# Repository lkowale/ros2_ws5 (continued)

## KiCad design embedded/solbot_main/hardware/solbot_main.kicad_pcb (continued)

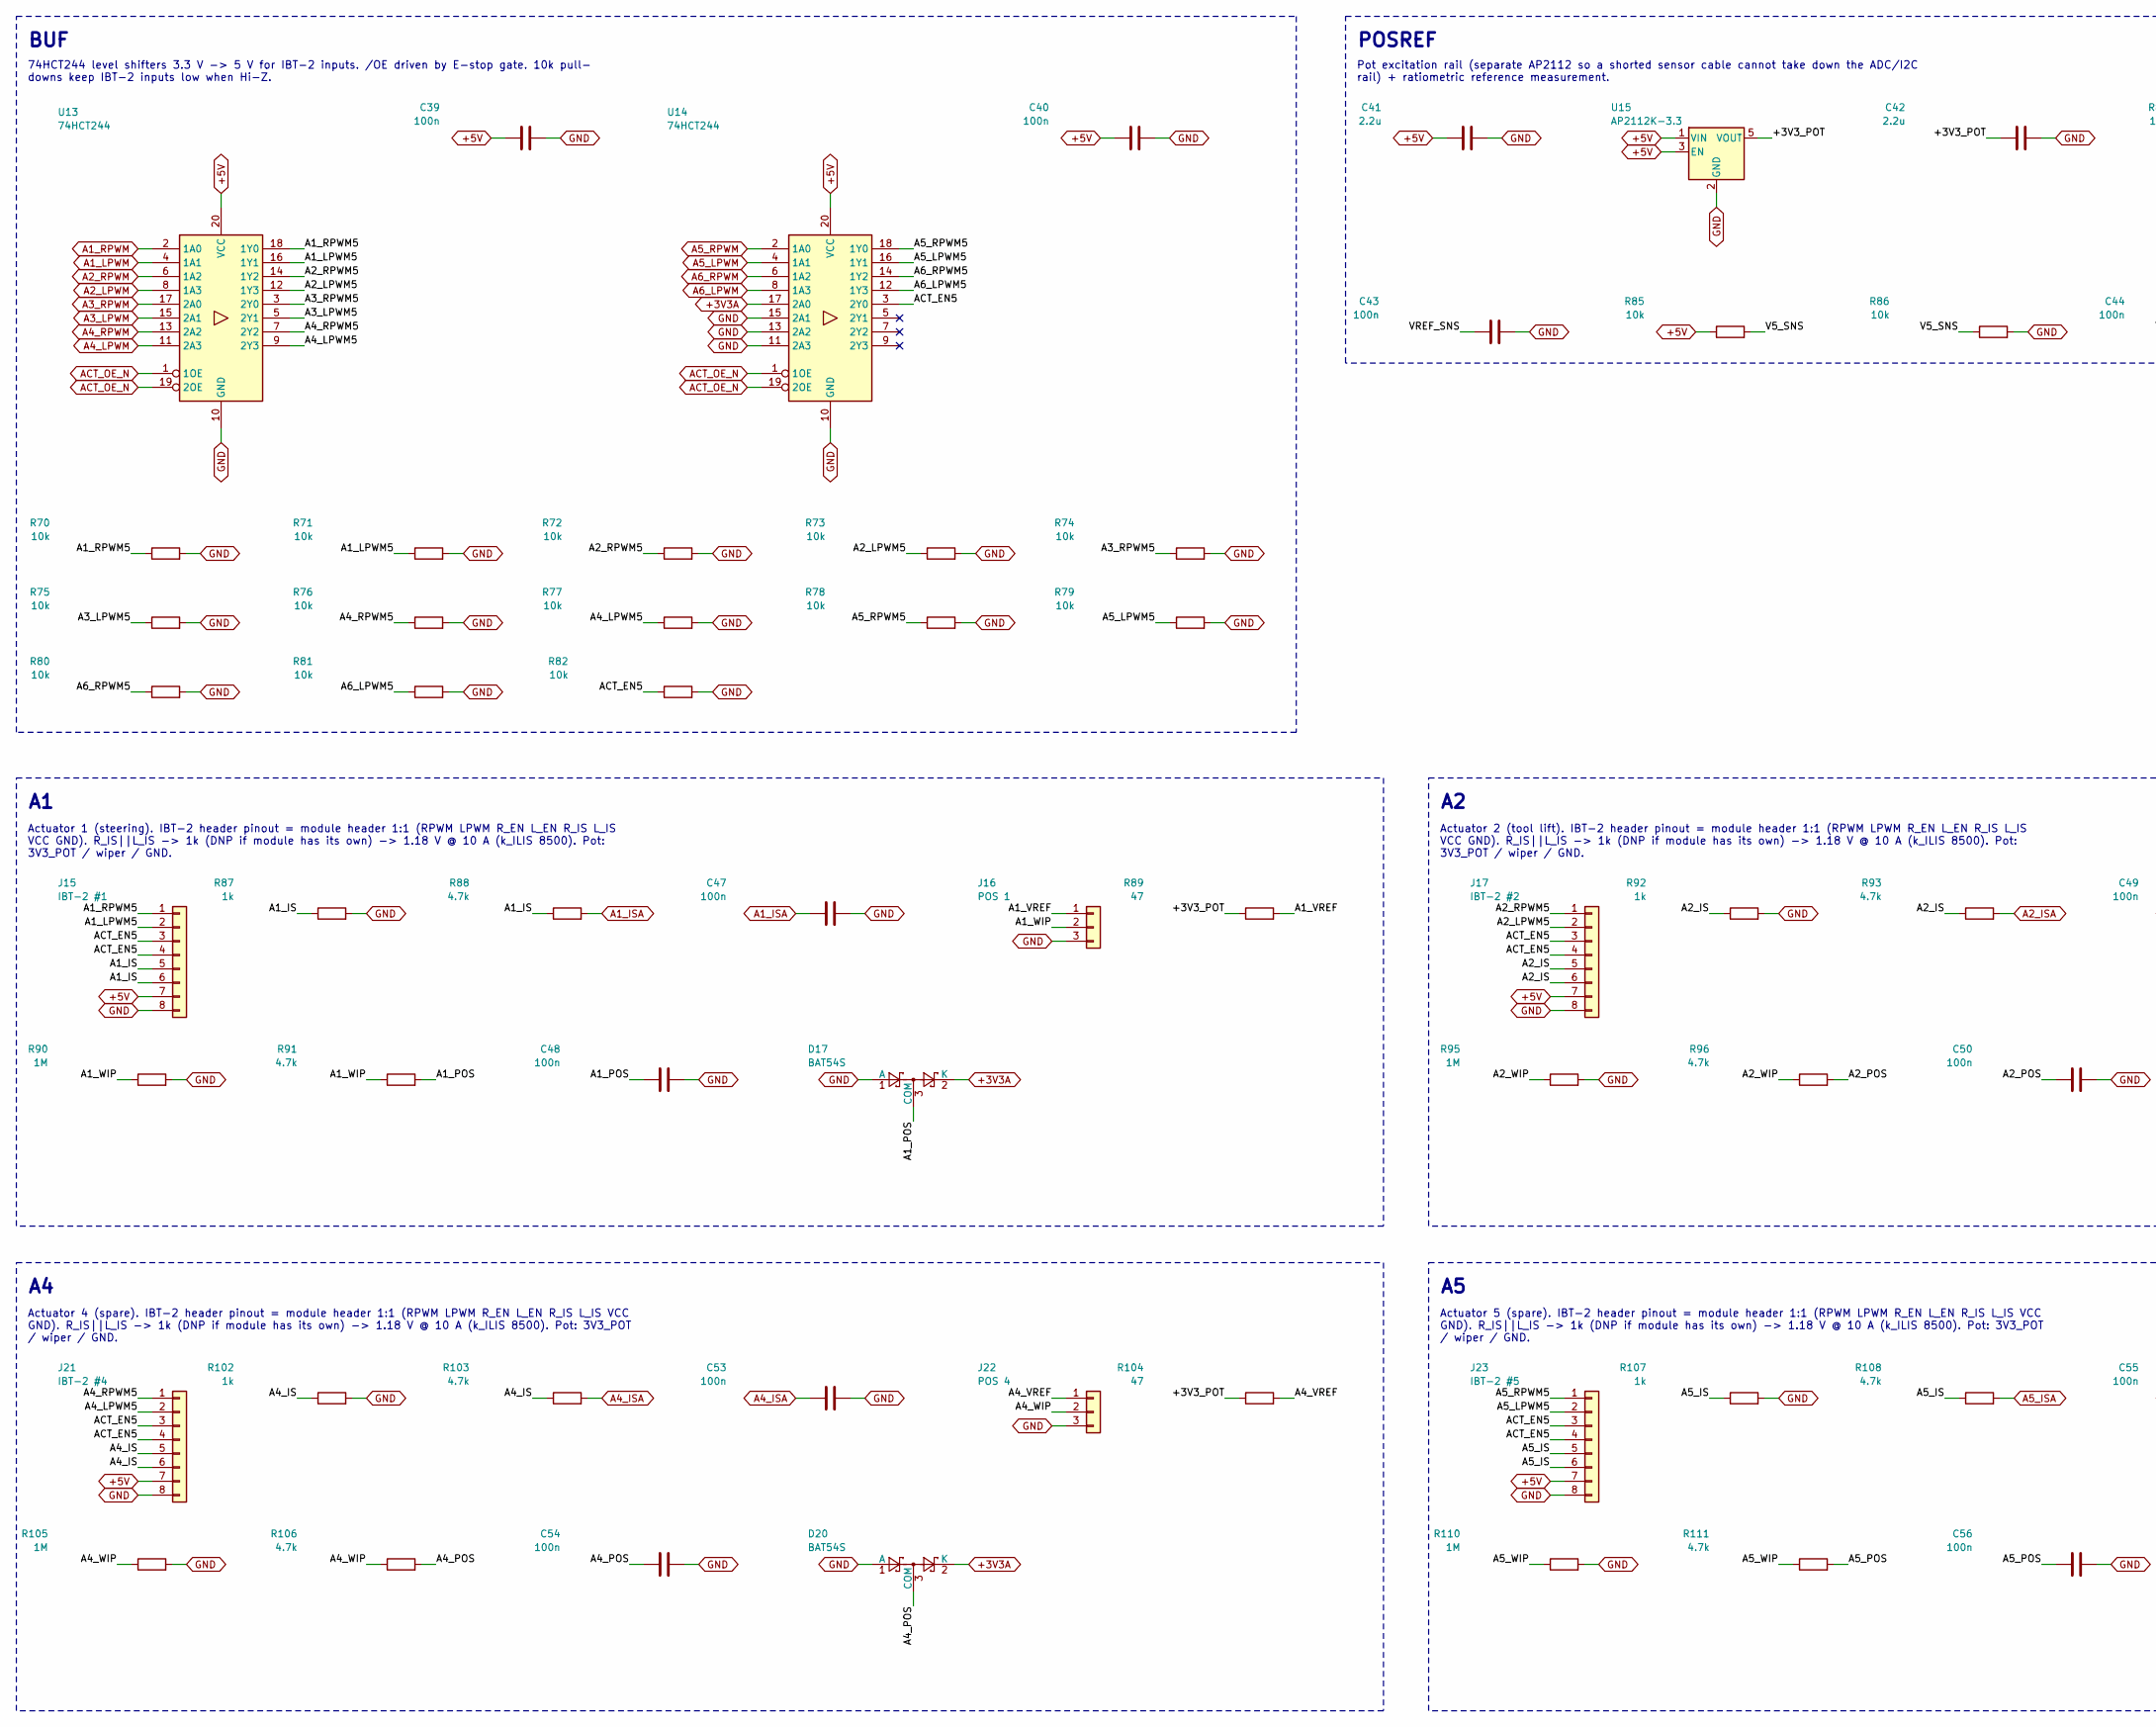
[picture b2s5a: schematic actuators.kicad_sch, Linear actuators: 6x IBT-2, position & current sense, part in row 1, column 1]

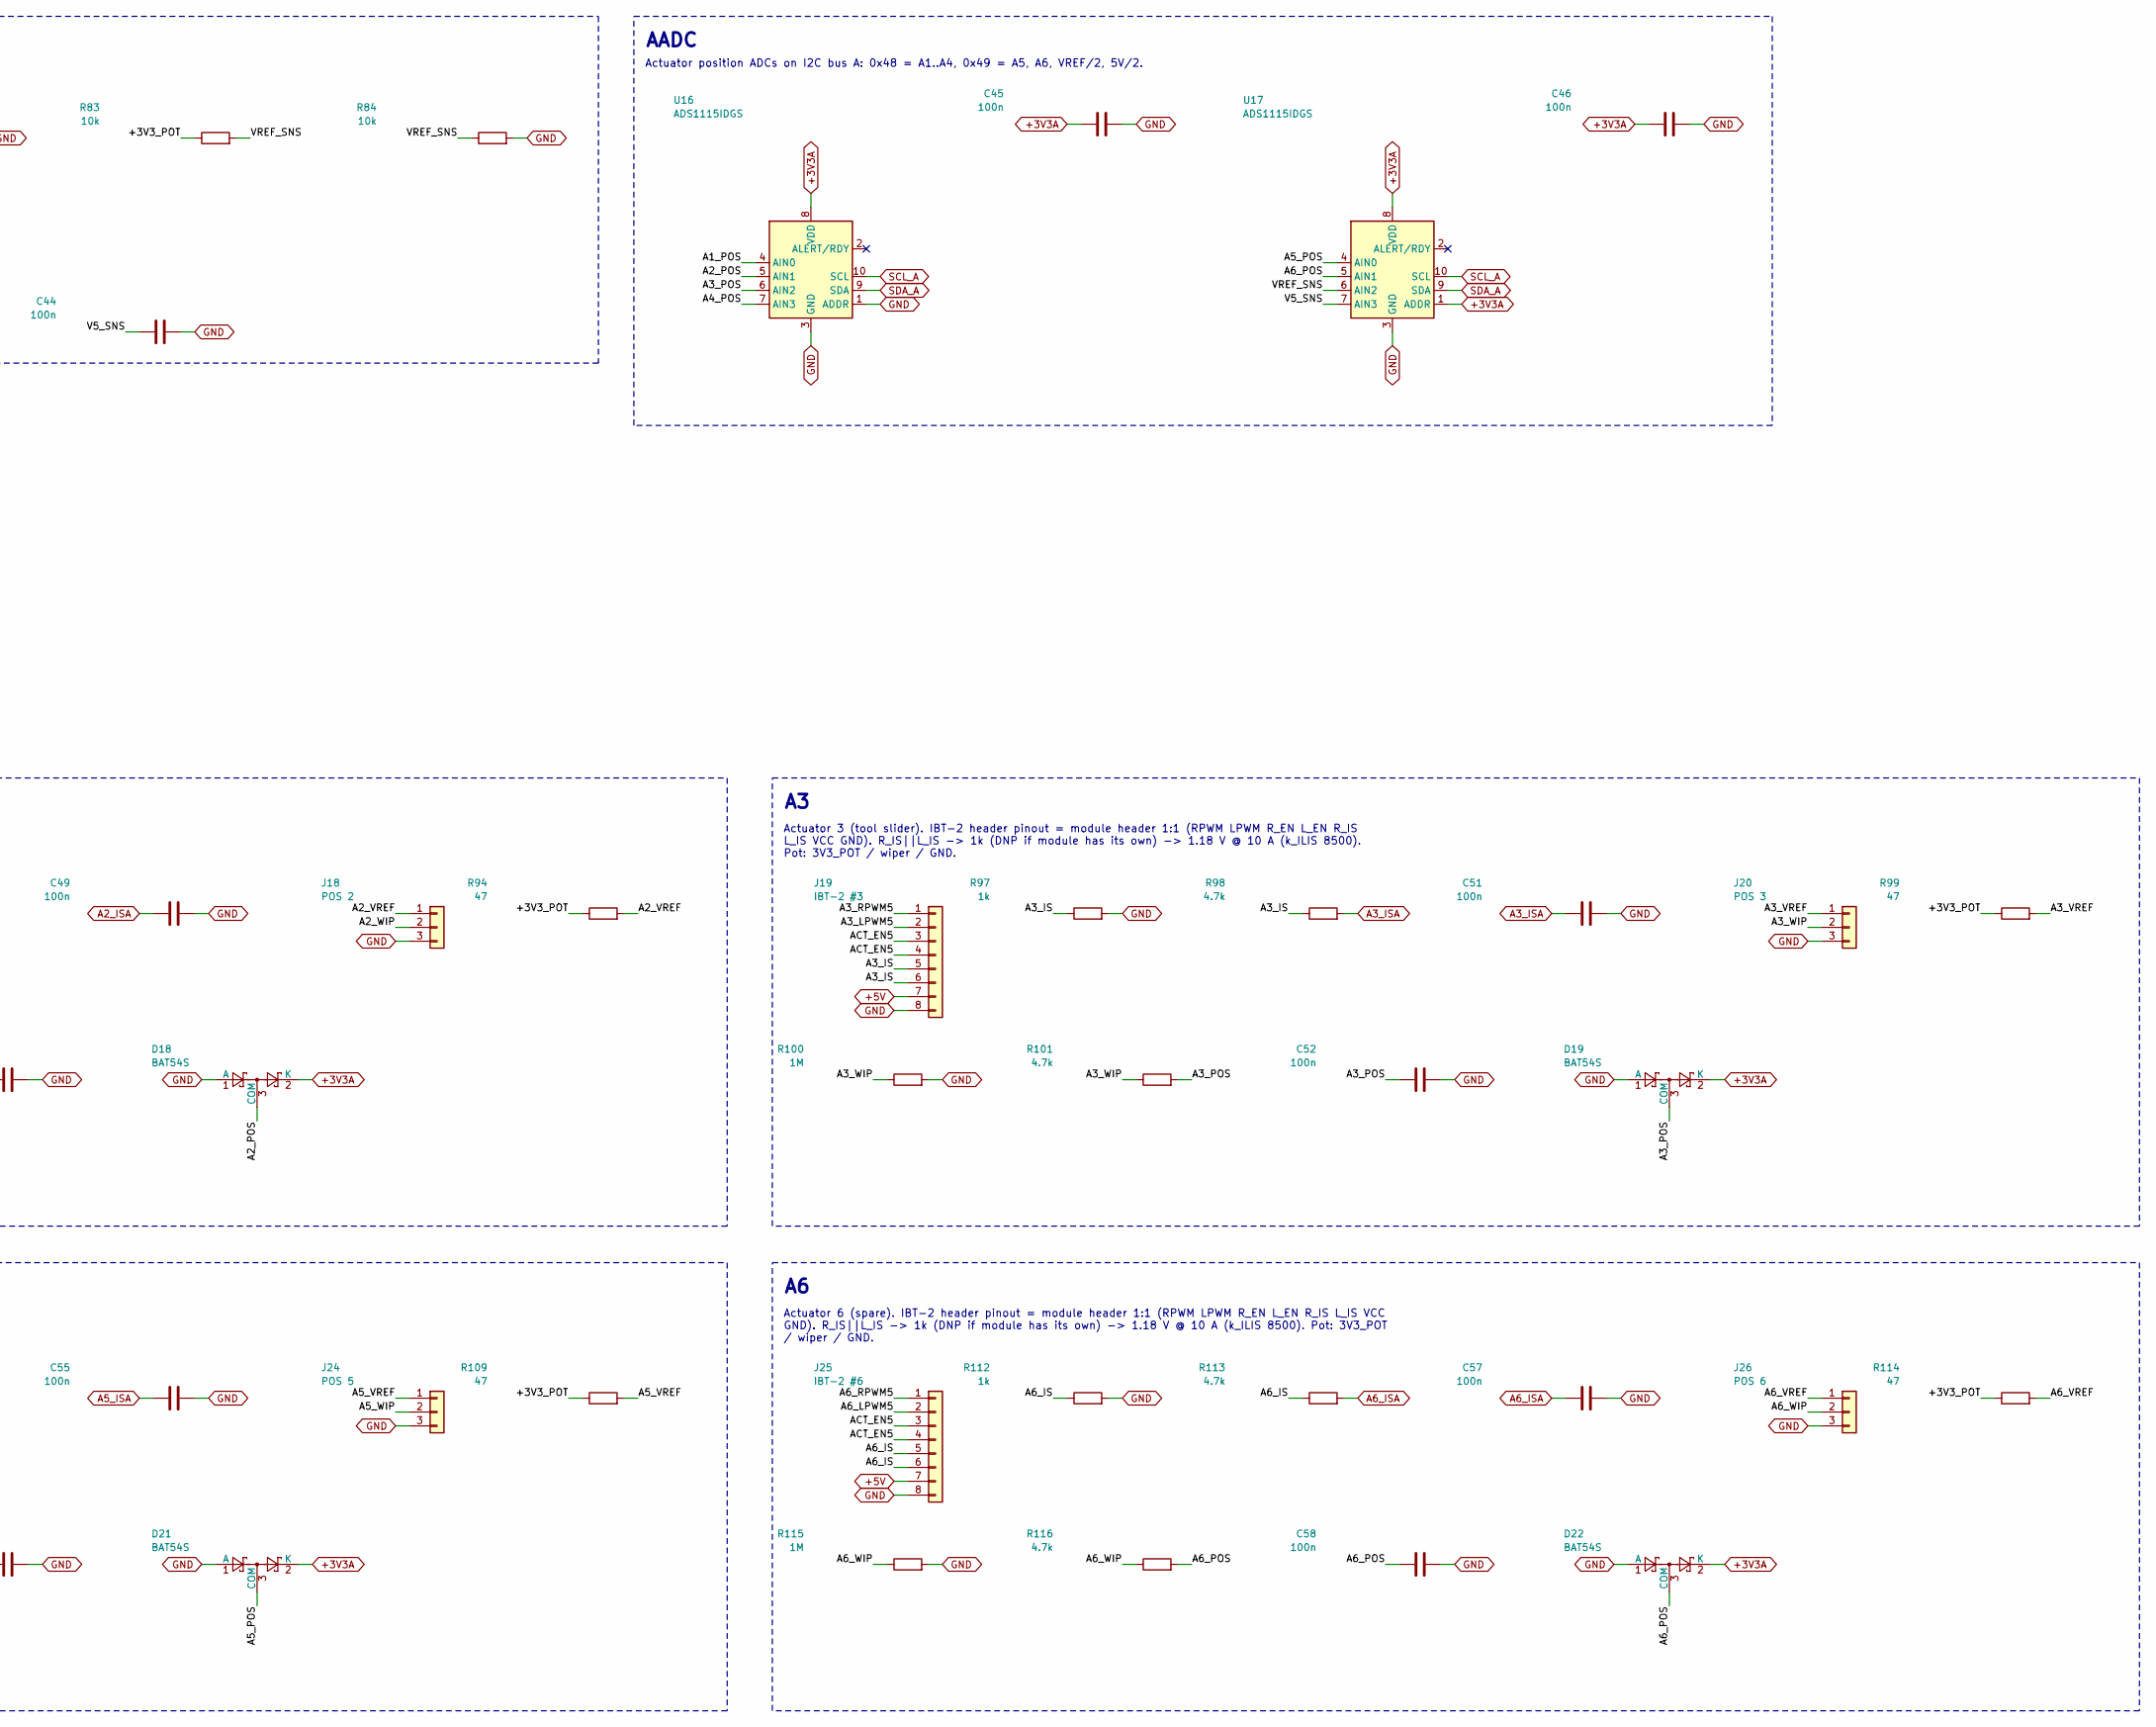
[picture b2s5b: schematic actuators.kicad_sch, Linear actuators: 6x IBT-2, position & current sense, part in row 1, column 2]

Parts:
C39, C40, C43, C44, C45, C46, C47, C48, C49, C50, C51, C52, C53, C54, C55, C56, C57, C58: 100n; C_0603_1608Metric
C41, C42: 2.2u; C_0805_2012Metric
D17, D18, D19, D20, D21, D22: BAT54S; SOT-23
J15: IBT-2 #1; PinHeader_1x08_P2.54mm_Vertical
J16: POS 1; TerminalBlock_Phoenix_PT-1,5-3-3.5-H_1x03_P3.50mm_Horizontal
J17: IBT-2 #2; PinHeader_1x08_P2.54mm_Vertical
J18: POS 2; TerminalBlock_Phoenix_PT-1,5-3-3.5-H_1x03_P3.50mm_Horizontal
J19: IBT-2 #3; PinHeader_1x08_P2.54mm_Vertical
J20: POS 3; TerminalBlock_Phoenix_PT-1,5-3-3.5-H_1x03_P3.50mm_Horizontal
J21: IBT-2 #4; PinHeader_1x08_P2.54mm_Vertical
J22: POS 4; TerminalBlock_Phoenix_PT-1,5-3-3.5-H_1x03_P3.50mm_Horizontal
J23: IBT-2 #5; PinHeader_1x08_P2.54mm_Vertical
J24: POS 5; TerminalBlock_Phoenix_PT-1,5-3-3.5-H_1x03_P3.50mm_Horizontal
J25: IBT-2 #6; PinHeader_1x08_P2.54mm_Vertical
J26: POS 6; TerminalBlock_Phoenix_PT-1,5-3-3.5-H_1x03_P3.50mm_Horizontal
R70, R71, R72, R73, R74, R75, R76, R77, R78, R79, R80, R81, R82, R83, R84, R85, R86: 10k; R_0603_1608Metric
R87, R92, R97, R102, R107, R112: 1k; R_0603_1608Metric
R88, R91, R93, R96, R98, R101, R103, R106, R108, R111, R113, R116: 4.7k; R_0603_1608Metric
R89, R94, R99, R104, R109, R114: 47; R_0603_1608Metric
R90, R95, R100, R105, R110, R115: 1M; R_0603_1608Metric
U13, U14: 74HCT244; SOIC-20W_7.5x12.8mm_P1.27mm
U15: AP2112K-3.3; SOT-23-5
U16, U17: ADS1115IDGS; TSSOP-10_3x3mm_P0.5mm

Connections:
+3V3A: C45.1, C46.1, D17.2 (K), D18.2 (K), D19.2 (K), D20.2 (K), D21.2 (K), D22.2 (K), U14.17 (2A0), U16.8 (VDD), U17.1 (ADDR), U17.8 (VDD); also elsewhere on the board
+3V3_POT: C42.1, R83.1, R89.1, R94.1, R99.1, R104.1, R109.1, R114.1, U15.5 (VOUT)
+5V: C39.1, C40.1, C41.1, J15.7, J17.7, J19.7, J21.7, J23.7, J25.7, R85.1, U13.20 (VCC), U14.20 (VCC), U15.1 (VIN), U15.3 (EN); also elsewhere on the board
A1_IS: J15.5, J15.6, R87.1, R88.1
A1_ISA: C47.1, R88.2; also elsewhere on the board
A1_LPWM: U13.4 (1A1); also elsewhere on the board
A1_LPWM5: J15.2, R71.1, U13.16 (1Y1)
A1_POS: C48.1, D17.3 (COM), R91.2, U16.4 (AIN0)
A1_RPWM: U13.2 (1A0); also elsewhere on the board
A1_RPWM5: J15.1, R70.1, U13.18 (1Y0)
A1_VREF: J16.1, R89.2
A1_WIP: J16.2, R90.1, R91.1
A2_IS: J17.5, J17.6, R92.1, R93.1
A2_ISA: C49.1, R93.2; also elsewhere on the board
A2_LPWM: U13.8 (1A3); also elsewhere on the board
A2_LPWM5: J17.2, R73.1, U13.12 (1Y3)
A2_POS: C50.1, D18.3 (COM), R96.2, U16.5 (AIN1)
A2_RPWM: U13.6 (1A2); also elsewhere on the board
A2_RPWM5: J17.1, R72.1, U13.14 (1Y2)
A2_VREF: J18.1, R94.2
A2_WIP: J18.2, R95.1, R96.1
A3_IS: J19.5, J19.6, R97.1, R98.1
A3_ISA: C51.1, R98.2; also elsewhere on the board
A3_LPWM: U13.15 (2A1); also elsewhere on the board
A3_LPWM5: J19.2, R75.1, U13.5 (2Y1)
A3_POS: C52.1, D19.3 (COM), R101.2, U16.6 (AIN2)
A3_RPWM: U13.17 (2A0); also elsewhere on the board
A3_RPWM5: J19.1, R74.1, U13.3 (2Y0)
A3_VREF: J20.1, R99.2
A3_WIP: J20.2, R100.1, R101.1
A4_IS: J21.5, J21.6, R102.1, R103.1
A4_ISA: C53.1, R103.2; also elsewhere on the board
A4_LPWM: U13.11 (2A3); also elsewhere on the board
A4_LPWM5: J21.2, R77.1, U13.9 (2Y3)
A4_POS: C54.1, D20.3 (COM), R106.2, U16.7 (AIN3)
A4_RPWM: U13.13 (2A2); also elsewhere on the board
A4_RPWM5: J21.1, R76.1, U13.7 (2Y2)
A4_VREF: J22.1, R104.2
A4_WIP: J22.2, R105.1, R106.1
A5_IS: J23.5, J23.6, R107.1, R108.1
A5_ISA: C55.1, R108.2; also elsewhere on the board
A5_LPWM: U14.4 (1A1); also elsewhere on the board
A5_LPWM5: J23.2, R79.1, U14.16 (1Y1)
A5_POS: C56.1, D21.3 (COM), R111.2, U17.4 (AIN0)
A5_RPWM: U14.2 (1A0); also elsewhere on the board
A5_RPWM5: J23.1, R78.1, U14.18 (1Y0)
A5_VREF: J24.1, R109.2
A5_WIP: J24.2, R110.1, R111.1
A6_IS: J25.5, J25.6, R112.1, R113.1
A6_ISA: C57.1, R113.2; also elsewhere on the board
A6_LPWM: U14.8 (1A3); also elsewhere on the board
A6_LPWM5: J25.2, R81.1, U14.12 (1Y3)
A6_POS: C58.1, D22.3 (COM), R116.2, U17.5 (AIN1)
A6_RPWM: U14.6 (1A2); also elsewhere on the board
A6_RPWM5: J25.1, R80.1, U14.14 (1Y2)
A6_VREF: J26.1, R114.2
A6_WIP: J26.2, R115.1, R116.1
ACT_EN5: J15.3, J15.4, J17.3, J17.4, J19.3, J19.4, J21.3, J21.4, J23.3, J23.4, J25.3, J25.4, R82.1, U14.3 (2Y0)
ACT_OE_N: U13.1 (1OE), U13.19 (2OE), U14.1 (1OE), U14.19 (2OE); also elsewhere on the board
GND: C39.2, C40.2, C41.2, C42.2, C43.2, C44.2, C45.2, C46.2, C47.2, C48.2, C49.2, C50.2, C51.2, C52.2, C53.2, C54.2, C55.2, C56.2, C57.2, C58.2, D17.1 (A), D18.1 (A), D19.1 (A), D20.1 (A), D21.1 (A), D22.1 (A), J15.8, J16.3, J17.8, J18.3, J19.8, J20.3, J21.8, J22.3, J23.8, J24.3, J25.8, J26.3, R70.2, R71.2, R72.2, R73.2, R74.2, R75.2, R76.2, R77.2, R78.2, R79.2, R80.2, R81.2, R82.2, R84.2, R86.2, R87.2, R90.2, R92.2, R95.2, R97.2, R100.2, R102.2, R105.2, R107.2, R110.2, R112.2, R115.2, U13.10 (GND), U14.10 (GND), U14.11 (2A3), U14.13 (2A2), U14.15 (2A1), U15.2 (GND), U16.1 (ADDR), U16.3 (GND), U17.3 (GND); also elsewhere on the board
SCL_A: U16.10 (SCL), U17.10 (SCL); also elsewhere on the board
SDA_A: U16.9 (SDA), U17.9 (SDA); also elsewhere on the board
V5_SNS: C44.1, R85.2, R86.1, U17.7 (AIN3)
VREF_SNS: C43.1, R83.2, R84.1, U17.6 (AIN2)

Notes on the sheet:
BUF
74HCT244 level shifters 3.3 V -> 5 V for IBT-2 inputs. /OE driven by E-stop gate. 10k pull- downs keep IBT-2 inputs low when Hi-Z.
POSREF
Pot excitation rail (separate AP2112 so a shorted sensor cable cannot take down the ADC/I2C rail) + ratiometric reference measurement.
AADC
Actuator position ADCs on I2C bus A: 0x48 = A1..A4, 0x49 = A5, A6, VREF/2, 5V/2.
Actuator 1 (steering). IBT-2 header pinout = module header 1:1 (RPWM LPWM R_EN L_EN R_IS L_IS VCC GND). R_IS||L_IS -> 1k (DNP if module has its own) -> 1.18 V @ 10 A (k_ILIS 8500). Pot: 3V3_POT / wiper / GND.
Actuator 2 (tool lift). IBT-2 header pinout = module header 1:1 (RPWM LPWM R_EN L_EN R_IS L_IS VCC GND). R_IS||L_IS -> 1k (DNP if module has its own) -> 1.18 V @ 10 A (k_ILIS 8500). Pot: 3V3_POT / wiper / GND.
Actuator 3 (tool slider). IBT-2 header pinout = module header 1:1 (RPWM LPWM R_EN L_EN R_IS L_IS VCC GND). R_IS||L_IS -> 1k (DNP if module has its own) -> 1.18 V @ 10 A (k_ILIS 8500). Pot: 3V3_POT / wiper / GND.
Actuator 4 (spare). IBT-2 header pinout = module header 1:1 (RPWM LPWM R_EN L_EN R_IS L_IS VCC GND). R_IS||L_IS -> 1k (DNP if module has its own) -> 1.18 V @ 10 A (k_ILIS 8500). Pot: 3V3_POT / wiper / GND.
Actuator 5 (spare). IBT-2 header pinout = module header 1:1 (RPWM LPWM R_EN L_EN R_IS L_IS VCC GND). R_IS||L_IS -> 1k (DNP if module has its own) -> 1.18 V @ 10 A (k_ILIS 8500). Pot: 3V3_POT / wiper / GND.
Actuator 6 (spare). IBT-2 header pinout = module header 1:1 (RPWM LPWM R_EN L_EN R_IS L_IS VCC GND). R_IS||L_IS -> 1k (DNP if module has its own) -> 1.18 V @ 10 A (k_ILIS 8500). Pot: 3V3_POT / wiper / GND.

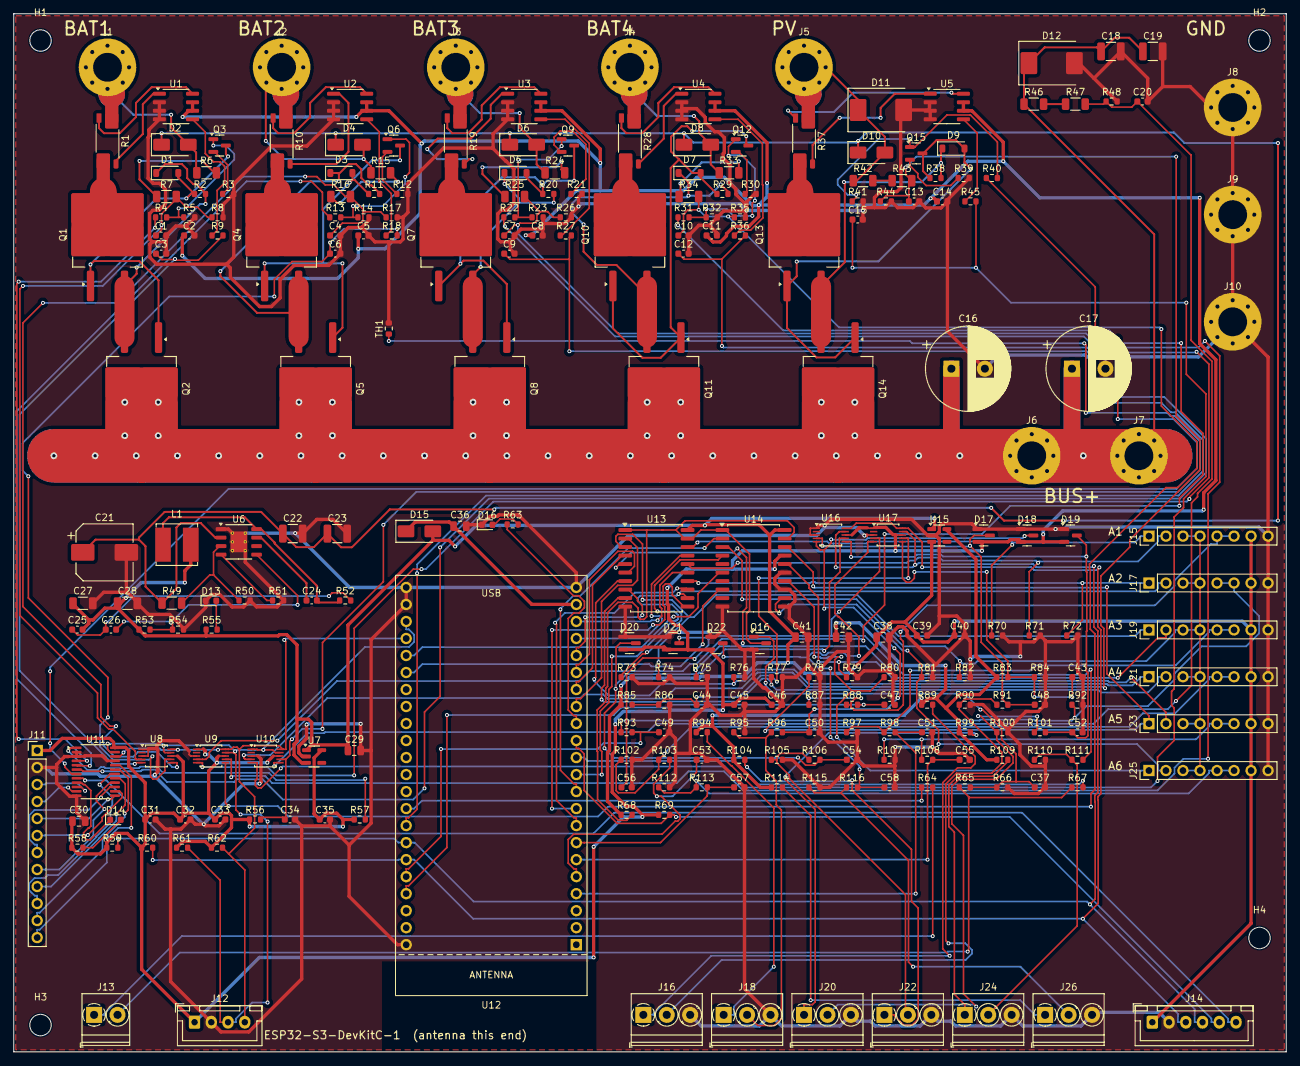
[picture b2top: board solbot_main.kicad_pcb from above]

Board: 2 copper layers, 190.0 x 155.0 mm, 261 parts (0 on the bottom side), 166 nets.

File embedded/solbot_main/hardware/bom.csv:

Qty,Value,Footprint,MPN / note,References
40,100n,C_0603_1608Metric,,C1 C2 C3 C4 C5 C6 C7 C8 C9 C10 C11 C12 C13 C14 C15 C20 C31 C32 C33 C34 C35 C37 C39 C40 C43 C44 C45 C46 C47 C48 C49 C50 C51 C52 C53 C54 C55 C56 C57 C58
2,100u 100V,CP_Radial_D12.5mm_P5.00mm,,C16 C17
2,10u,C_0805_2012Metric,,C36 C38
1,180p,C_0603_1608Metric,,C26
2,1u 100V,C_1210_3225Metric,,C18 C19
1,2.2n 50V,C_0603_1608Metric,,C24
4,2.2u,C_0805_2012Metric,,C29 C30 C41 C42
2,2.2u 100V,C_1210_3225Metric,,C22 C23
1,22u 100V,CP_Elec_8x10,,C21
2,22u 25V,C_1206_3216Metric,,C27 C28
1,3.3n,C_0603_1608Metric,,C25
5,12V BZT52C12,D_SOD-123,,D1 D3 D5 D7 D9
6,BAT54S,SOT-23,,D17 D18 D19 D20 D21 D22
5,ES1D (200 V 1 A),D_SMA,,D2 D4 D6 D8 D10
1,SMCJ58A (TVS),D_SMC,,D12
1,"SMCJ58A (TVS, reverse-PV clamp)",D_SMC,,D11
1,SS34 (blocks USB back-feed),D_SMA,,D15
1,green 5V,LED_0603_1608Metric,,D13
1,red ERR,LED_0603_1608Metric,,D16
1,yellow PWR-STAT,LED_0603_1608Metric,,D14
1,BAT1+ (M4 lug),MountingHole_4.3mm_M4_Pad_Via,,J1
1,BAT2+ (M4 lug),MountingHole_4.3mm_M4_Pad_Via,,J2
1,BAT3+ (M4 lug),MountingHole_4.3mm_M4_Pad_Via,,J3
1,BAT4+ (M4 lug),MountingHole_4.3mm_M4_Pad_Via,,J4
2,BUS+ (M4 lug),MountingHole_4.3mm_M4_Pad_Via,,J6 J7
1,E-STOP (NC loop),"TerminalBlock_Phoenix_PT-1,5-2-3.5-H_1x02_P3.50mm_Horizontal",,J13
1,EXP IO,PinHeader_1x12_P2.54mm_Vertical,,J11
3,GND (M4 lug),MountingHole_4.3mm_M4_Pad_Via,,J8 J9 J10
1,I2C-B ext,JST_XH_B4B-XH-A_1x04_P2.50mm_Vertical,,J12
1,IBT-2 #1,PinHeader_1x08_P2.54mm_Vertical,,J15
1,IBT-2 #2,PinHeader_1x08_P2.54mm_Vertical,,J17
1,IBT-2 #3,PinHeader_1x08_P2.54mm_Vertical,,J19
1,IBT-2 #4,PinHeader_1x08_P2.54mm_Vertical,,J21
1,IBT-2 #5,PinHeader_1x08_P2.54mm_Vertical,,J23
1,IBT-2 #6,PinHeader_1x08_P2.54mm_Vertical,,J25
1,IMU BNO085,JST_XH_B6B-XH-A_1x06_P2.50mm_Vertical,,J14
1,POS 1,"TerminalBlock_Phoenix_PT-1,5-3-3.5-H_1x03_P3.50mm_Horizontal",,J16
1,POS 2,"TerminalBlock_Phoenix_PT-1,5-3-3.5-H_1x03_P3.50mm_Horizontal",,J18
1,POS 3,"TerminalBlock_Phoenix_PT-1,5-3-3.5-H_1x03_P3.50mm_Horizontal",,J20
1,POS 4,"TerminalBlock_Phoenix_PT-1,5-3-3.5-H_1x03_P3.50mm_Horizontal",,J22
1,POS 5,"TerminalBlock_Phoenix_PT-1,5-3-3.5-H_1x03_P3.50mm_Horizontal",,J24
1,POS 6,"TerminalBlock_Phoenix_PT-1,5-3-3.5-H_1x03_P3.50mm_Horizontal",,J26
1,PV+ (M4 lug),MountingHole_4.3mm_M4_Pad_Via,,J5
1,47u 1.5A SRN6045TA-470M,L_Bourns_SRN6045TA,,L1
1,2N7002,SOT-23,,Q16
5,MMBTA42 (300 V),SOT-23,,Q3 Q6 Q9 Q12 Q15
10,SQM120P10_10M1L,TO-263-2,"Vishay SQM120P10_10M1L (-100 V, 10 mOhm)",Q1 Q2 Q4 Q5 Q7 Q8 Q10 Q11 Q13 Q14
5,1.2k,R_0603_1608Metric,,R3 R12 R21 R30 R39
6,100k,R_0603_1608Metric,,R5 R14 R23 R32 R41 R66
27,10k,R_0603_1608Metric,,R2 R11 R20 R29 R38 R56 R57 R67 R68 R69 R70 R71 R72 R73 R74 R75 R76 R77 R78 R79 R80 R81 R82 R83 R84 R85 R86
1,158k,R_0603_1608Metric,,R53
1,1M,R_1206_3216Metric,,R49
6,1M,R_0603_1608Metric,,R90 R95 R100 R105 R110 R115
19,1k,R_0603_1608Metric,,R4 R9 R13 R18 R22 R27 R31 R36 R40 R45 R58 R63 R65 R87 R92 R97 R102 R107 R112
5,1m 1% WSK2512,R_Shunt_Vishay_WSK2512_6332Metric_T1.19mm,Vishay WSK25121L000FEA,R1 R10 R19 R28 R37
1,2.2k,R_0603_1608Metric,,R55
1,221k,R_0603_1608Metric,,R52
6,33k 0.1%,R_0603_1608Metric,,R8 R17 R26 R35 R44 R48
16,4.7k,R_0603_1608Metric,,R59 R60 R61 R62 R88 R91 R93 R96 R98 R101 R103 R106 R108 R111 R113 R116
1,41.2k,R_0603_1608Metric,,R51
6,47,R_0603_1608Metric,,R89 R94 R99 R104 R109 R114
1,470,R_0603_1608Metric,,R64
1,49.9k,R_0603_1608Metric,,R54
12,499k,R_1206_3216Metric,,R6 R7 R15 R16 R24 R25 R33 R34 R42 R43 R46 R47
1,91k,R_0603_1608Metric,,R50
1,10k B3950 (place near FETs),R_0603_1608Metric,,TH1
2,74HCT244,SOIC-20W_7.5x12.8mm_P1.27mm,,U13 U14
5,ADS1115IDGS,TSSOP-10_3x3mm_P0.5mm,,U8 U9 U10 U16 U17
2,AP2112K-3.3,SOT-23-5,,U7 U15
1,ESP32-S3-DevKitC-1,ESP32-S3-DevKitC-1_Socket,,U12
5,INA241A2xD,SOIC-8_3.9x4.9mm_P1.27mm,,U1 U2 U3 U4 U5
1,LM5164DDAR,HSOP-8-1EP_3.9x4.9mm_P1.27mm_EP2.41x3.1mm_ThermalVias,,U6
1,TCA9535PWR,TSSOP-24_4.4x7.8mm_P0.65mm,,U11

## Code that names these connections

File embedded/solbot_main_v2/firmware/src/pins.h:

// Pin map for solbot_main v2 rev B PCB (see hardware/solbot_main_v2.kicad_sch, root sheet).
#pragma once
#include <stdint.h>

namespace pins {

constexpr int I2C_SDA = 41;      // BNO085 (0x4A)
constexpr int I2C_SCL = 42;

constexpr int ACT_EN = 39;       // high = actuators allowed (through E-stop loop -> IBT-2 R_EN/L_EN)
constexpr int ESTOP_SENSE = 40;  // high = E-stop loop closed
constexpr int BUS_VS = 9;        // ADC1: main bus / 32.33
constexpr int V12_SNS = 10;      // ADC1: 12 V rail / 11
constexpr int SSR1 = 21;         // PV SSR, high = on
constexpr int SSR2 = 47;         // second SSR (back-to-back PV pair or spare)
constexpr int IMU_INT = 20;
constexpr int IMU_RST = 19;      // active low
constexpr int LED_ERR = 46;      // red LED, active high

constexpr int NACT = 4;
struct ActPins {
  int rpwm, lpwm, is_adc, pos_adc;
};
// A1..A4. PWM pins are ACTIVE-LOW (74HC14 inverter in front of the IBT-2).
// is_adc: IBT-2 IS voltage (1k -> 8.5 A/V), pos_adc: sensor wiper x POS_DIV (5 V sensor -> 3.0 V)
constexpr ActPins ACT[NACT] = {{11, 12, 5, 1}, {13, 14, 6, 2}, {15, 16, 7, 3}, {17, 18, 8, 4}};
// rev C optional ADS1115 module (J15): module input A0..A3 for actuator A1..A4, in PCB routing order
// (socket: A0 = A4_WIP, A1 = A2_WIP, A2 = A3_WIP, A3 = A1_WIP: raw 0..5 V, module on +5V)
constexpr uint8_t ADS_CH[NACT] = {3, 1, 2, 0};
// ESP ADC sees the wiper through a 100k/150k divider (5 V sensors -> 3.0 V); the ADS1115 sees it raw
constexpr float POS_DIV = 150.0f / 250.0f;

}  // namespace pins

namespace i2caddr {
constexpr uint8_t BNO085 = 0x4A;
}  // namespace i2caddr

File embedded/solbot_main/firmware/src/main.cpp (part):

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static volatile bool imuOk = false;
static volatile bool imuResetReq = false;
static volatile uint32_t i2cErrA = 0, i2cErrB = 0;
static float vrefPotRatio = 0;            // VREF_SNS raw (= VREF/2) counts
static int16_t v5Raw = 0;

static const char *DEFAULT_NAMES[6] = {"steer", "lift", "slider", "a4", "a5", "a6"};
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    float amps[6];
    for (int i = 0; i < 6; i++) amps[i] = analogReadMilliVolts(pins::ACT[i].is_adc) * 0.0085f;

    estopOk = digitalRead(pins::ESTOP_SENSE);
    bool allowed = actEnable && estopOk;
    float duty[6];
    {
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      }
    }
    for (int i = 0; i < 6; i++) hbridge::write(i, duty[i]);
    digitalWrite(pins::ACT_EN, actEnable ? HIGH : LOW);
  }
}

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      pvOn = pm.pv.on;
    }
    if (tca.ok()) applySwitches(want);
    digitalWrite(pins::PV_EN, pvOn ? HIGH : LOW);

    if (imuResetReq) {
      imuResetReq = false;
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      tca.set(expbit::LED_PWR, !(anyOn && (now / 500) % 2));  // blink while a pack is connected
      bool fault = !estopOk || !imuOk;
      for (auto &a : act) fault |= a.st.fault != ActFault::NONE;
      digitalWrite(pins::LED_ERR, fault);
    }
  }
}
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// ------------------------------------------------------------------ setup / loop
void setup() {
  Serial.begin(115200);
  pinMode(pins::ACT_EN, OUTPUT);
  digitalWrite(pins::ACT_EN, LOW);
  pinMode(pins::PV_EN, OUTPUT);
  digitalWrite(pins::PV_EN, LOW);
  pinMode(pins::LED_ERR, OUTPUT);
  pinMode(pins::ESTOP_SENSE, INPUT);
  pinMode(pins::IMU_INT, INPUT);
  for (auto &p : pins::ACT) analogSetPinAttenuation(p.is_adc, ADC_11db);
  hbridge::begin(20000);
  gLock = xSemaphoreCreateMutex();
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
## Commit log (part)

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2026-06-15 Restructure src/ to mirror ros2_ws4 layout, drop solbot5_ prefix
    Directory layout now matches ros2_ws4/src/:
    src/control/control/ (was src/solbot5_control/)
    src/description/description/ (was src/solbot5_description/)
    src/simulation/gazebo_spawn/ (was src/solbot5_gazebo_spawn/)
    src/navigation/localization/ (was src/solbot5_localization/)
    src/navigation/nav2_bringup/ (was src/solbot5_nav2_bringup/)
2026-06-15 Fix m3 launch: script +x bits, hardcoded nav2_bringup path in BT log
2026-06-15 Fix relposned_heading.py missing execute bit
2026-06-15 Add tool_link: symmetry line, ground plane, 80cm behind front axle
2026-06-16 Add ToolAnchoredRPPController: RPP anchored to configurable TF frame
    Same pattern as ws4 GpsAnchoredRPPController. Substitutes the pose of
    gps_frame_id (default gps_link, set to tool_link for implement following)
    into RPP geometry before computing velocity commands.
    Use for arc/RS path following where tool_link must track the path.
2026-06-16 Fix execute bits on control and localization Python files
2026-06-16 Add solbot5_msgs + one_line_nav: single-line swath navigator
    solbot5_msgs:
    RunOneLine.action — map-frame start/end points (x,y,yaw) or field_name
    one_line_nav:
    OneLineNavigator plugin (nav2_core::BehaviorTreeNavigator)
    - loads line.json with map-frame coords (no GPS->map conversion needed)
    - sets map_points on BT blackboard
2026-06-16 Add one_line_nav stack: SwathFollow controller, StraightLine planner, BT plugins, test field
    - nav2_params_m3: add run_one_line navigator (OneLineNavigator), SwathFollow controller
    (ToolLineFollowerController with gps_frame_id=gps_link), StraightLine planner,
    plugin_lib_names for one_line_bt_nodes BT custom nodes
    - run_m3_sim.sh: add `line [field_name]` sub-command, cancel also hits /run_one_line
    - src/fields/test_line/line.json: 20m north swath for sim testing
2026-06-16 Port RunOneLine to ws4 interface: GeoPoint goal + ConvertGeoPoints via fromLL
    - RunOneLine.action: replace x/y/yaw fields with GeoPoint start_point/end_point
    - Navigator: puts geo_points on blackboard (not map_points); loadLineFromFile uses lat/lon
    - bt_nodes: add ConvertGeoPoints (calls fromLL service), ReverseGeoPoints,
    GetGeoPointFromVector; keep ReversePoses/GetPoseFromPoses for internal map_points use
    - BT XMLs: ConvertGeoPoints called once at start of OneLineBT; TurnSwath reverses
    geo_points then re-converts to map frame
2026-06-16 Fix BT plugin export: add BT_PLUGIN_EXPORT so BT_RegisterNodesFromPlugin is visible
2026-06-16 test_line: start 2m ahead of robot, 6m long eastward
2026-06-16 Add robot_image plugin to mapviz_m3 config
2026-06-16 Replace robot_image with pose plugin on /robot_pose to fix sim-time blinking
2026-06-16 Add StraightLine planner to planner package — was missing from Jazzy system install
2026-06-16 Publish /plan_swath and /plan_turn topics; add both to mapviz_m3
2026-06-16 Add DriveArc behavior+BT node; replace SwathTurnPlanner with BT arc subtree
2026-06-16 Fix navsat_transform deadlock; segment-by-segment turn; approach path in mapviz
    Localization:
    - world_frame: map in navsat_transform (was: odom — caused EKF↔navsat deadlock)
    - Restore odometry/filtered->odom remapping on navsat_transform so it receives
    EKF output and sets has_transform_odom_ without waiting for GPS first
    - Reset ROS env vars in run_m3_sim.sh to prevent ws4 binary contamination
    Turn sequence (turn_swath.xml):
2026-06-16 Add 0.5m leadout straight before arc1 in SwathTurnPlanner seg1
    Seg1 now drives forward 0.5m along the swath bearing before starting the
    90° left arc, giving the robot clearance past the swath end before turning.
    Controlled by lead_out_length parameter (default 0.0, set to 0.5 for SwathTurn1).
2026-06-16 Add arc_goal_checker (position-only) for arc2 reverse path following
    Arc2 end poses have yaw flipped by π (RPP reverse convention). SimpleGoalChecker
    with yaw_goal_tolerance=0.5 never triggers — robot is at correct position but
    heading is π off from the path end pose. Use nav2_controller::PositionGoalChecker
    (xy_goal_tolerance=0.5, ignores yaw) for arc2 FollowPath.
2026-06-16 Increase arc1 sweep from 90° to 120°
2026-06-17 Add RS test suite mapviz config; auto-launch on test sub-command
    mapviz_rs_test.mvc: shows /plan_forward (green), /plan_reverse (red),
    /odom trail (red arrows), /gps/fix (green points), robot pose (orange arrow).
    Tailored for observing RS planner goals — no swath/turn path plugins.
    run_mapviz.sh: accepts config filename as $1 (e.g. mapviz_rs_test.mvc),
    falls back to M=2/3 selection if not provided.
    run_m3_sim.sh test: launches mapviz with RS test config in background
2026-06-17 Remove auto-launch of mapviz from test sub-command; document RS test config usage
2026-06-17 Fix RS planner reverse: yaw-flip poses on reverse segments; use arc_goal_checker
    Reverse segment poses now have yaw+π so RPP correctly drives backward (it
    detects reverse from yaw vs travel direction) and the goal checker matches
    the robot's actual heading at path end.
    navigate_plan_once: use arc_goal_checker (position-only) so goal fires
    regardless of whether the last segment is forward or reverse.
2026-06-17 Add all 12 RS word families (was: 5 of 12)
    Families added:
    6 CCSC L+R-S-L-
    7 CCSC L+R-S-R-
    8 CCSCC L+R-S-L-R+
    9 CCCC L+R+L-R-
    10 CCCC L+R-L-R+
2026-06-18 Add M3 sim thorough logger (m3_sim_logger.py + run_m3_logger.sh)
    Subscribes to all relevant topics and logs:
    - ODOM: map/odom TF pose (x, y, yaw, age)
    - EKF: /odom filtered pose, velocity, covariance diagonal
    - GPS: /gps/fix status, lat/lon, position covariance
    - CTRL: /cmd_vel commanded twist
    - PLAN: /plan_forward /plan_reverse /plan_swath /plan_turn (n_poses, length, start/end)
2026-06-18 Auto-start m3_sim_logger when running test subcommand
    Spawns the logger in background before the first goal, waits 2s for
    it to connect, then kills it cleanly after the test suite completes.
2026-06-18 Add start/goal arrow markers in mapviz for RS test suite
    goal_marker_publisher.py: listens to bt_navigator /rosout for
    "Begin navigating from (sx,sy) to (gx,gy)" and publishes a
    MarkerArray on /goal_markers — green ARROW at start, red ARROW
    at goal, transient_local so all goals accumulate across the run.
    Wired into m3_nav_sim.launch.py. mapviz_rs_test.mvc gets a
    mapviz_plugins/marker display on /goal_markers.
2026-06-18 Fix RS planner path discontinuity; fix goal marker arrows
    Planner: replace fixed-n sampling with a while-loop that emits steps
    at `step` intervals then one exact-remainder final step. This guarantees
    the last sampled point lands at the true geometric arc end with no gap,
    rather than landing up to one step short due to integer truncation.
    The trailing goal-snap append remains to close any residual gap.
    goal_marker_publisher: subscribe to NavigateToPose_SendGoal_Request
2026-06-18 Update mapviz_rs_test.mvc: add received_global_plan, robot trail+arrow, cleaner colors
2026-06-18 Fix goal markers: deduplicate by goal position not stamp
2026-06-18 Add mapviz_line.mvc for one-line navigator; add line/rs shorthands to run_mapviz.sh
2026-06-19 Add RsTestNavigator for sequential RS planner testing
    - New rs_test_nav package: BehaviorTreeNavigator<RunRsTest> that drives
    through a list of PoseStamped goals one by one using the RS planner.
    PopNextGoal BT node pops goals from blackboard; ForceSuccess around
    each sub-navigation so a failed goal advances to the next rather than
    aborting the suite.
    - New RunRsTest.action in solbot5_msgs: goal list + labels, feedback
2026-06-19 Replace hand-rolled RS formulas with OMPL backend
    The 12 RS word families implemented from scratch had systematic formula
    errors: wrong sign in the t derivation for CCC families (A+pi+u/2 vs
    A+pi-u/2), wrong v formula, and all CCSC/CSCC/CCCC families incorrect.
    This caused paths to end 12-15m from the goal — the planner fell back
    to appending a teleport jump to the last waypoint.
    Replace the custom RS solver with ompl::base::ReedsSheppStateSpace which
2026-06-19 Add CSV logger and /rs_ctrl_debug publisher for controller tuning
    Controller publishes per-cycle debug data on /rs_ctrl_debug (String CSV:
    idx, n, rev, cte, heading_err_rad, stanley_rad, v_cmd, w_cmd, dist_to_end).
    rs_controller_logger.py subscribes to that plus /odom, /gps/fix, /cmd_vel
    and TF (map→base_footprint, map→tool_link), writing 20 Hz rows to
    logs/m3_sim/rs_ctrl_<timestamp>.csv with a latest symlink.
2026-06-19 Add job tracking (path index, label, dist_remaining) and wall_time to CSV logger
    Subscribes to /run_rs_test/_action/feedback to get current_goal_index and
    current_label from the RS test suite navigator, so each CSV row knows which
    test path the controller is executing. Also adds wall_time column alongside
    ROS time_sec for easy correlation with terminal logs.
2026-06-19 Add tool_link and base_footprint live pose displays to Mapviz
    tf_pose_publisher.py now publishes both /robot_pose (base_footprint) and
    /tool_link_pose (rear axle) as PoseStamped at 20 Hz using Time(0) TF lookup,
    bypassing Mapviz's TF lag. mapviz_rs_test.mvc adds matching pose displays:
    blue dot for base_footprint, orange arrow for tool_link.
2026-06-19 Remove base_footprint pose display from Mapviz (redundant with gps/fix)
2026-06-19 Fix align-phase deadband trap and reverse detection
    Align phase: setPlan() was forcing aligning_=true, trapping paths where
    initial h_err is inside the 10°-30° hysteresis band (e.g. path0 stuck at
    11.5° forever spinning). Fix: start aligning_=false, let first cycle decide.
    Reverse detection: planner was storing cyaw+π for reverse waypoints (RPP
    convention). isReverse() compared wp_yaw vs geometric tangent — both equal
    cyaw+π on reverse, difference=0, so rev=false always. Fix: planner now
2026-06-19 Fix segment-boundary oscillation and mid-path align stalls
    closestIndex(): removed backward search (was allowing current_idx_-5 regression).
    Strictly forward-only search prevents oscillation at rev/fwd boundaries where
    robot is equidistant from last reverse and first forward waypoint, causing
    isReverse() and v_cmd sign to flip every cycle.
    Align phase: trigger on segment direction flip (rev!=prev_rev) in addition to
    h_err threshold, so transitions between reverse and forward segments get a
2026-06-19 Remove align phase (Ackermann can't rotate in place), raise k_cross_gain to 3.0
    Ackermann sim requires forward velocity to turn — spinning in place with v=0
    produces zero angular motion (confirmed: robot_yaw frozen at 150° with w=1.0).
    The align phase was stalling all paths: 68-91% of frames at v=0 doing nothing.
    Fix: remove align phase entirely. Stanley heading+CTE correction handles all
    misalignment while driving. Raised k_cross_gain 1.0→3.0 so CTE correction
    is strong enough to pull the robot onto arcs before drifting large.
